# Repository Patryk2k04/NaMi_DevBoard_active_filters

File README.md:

This is an example of using goldpin connectors on the edge of the STM_proto_board https://github.com/Patryk2k04/STM_proto_board

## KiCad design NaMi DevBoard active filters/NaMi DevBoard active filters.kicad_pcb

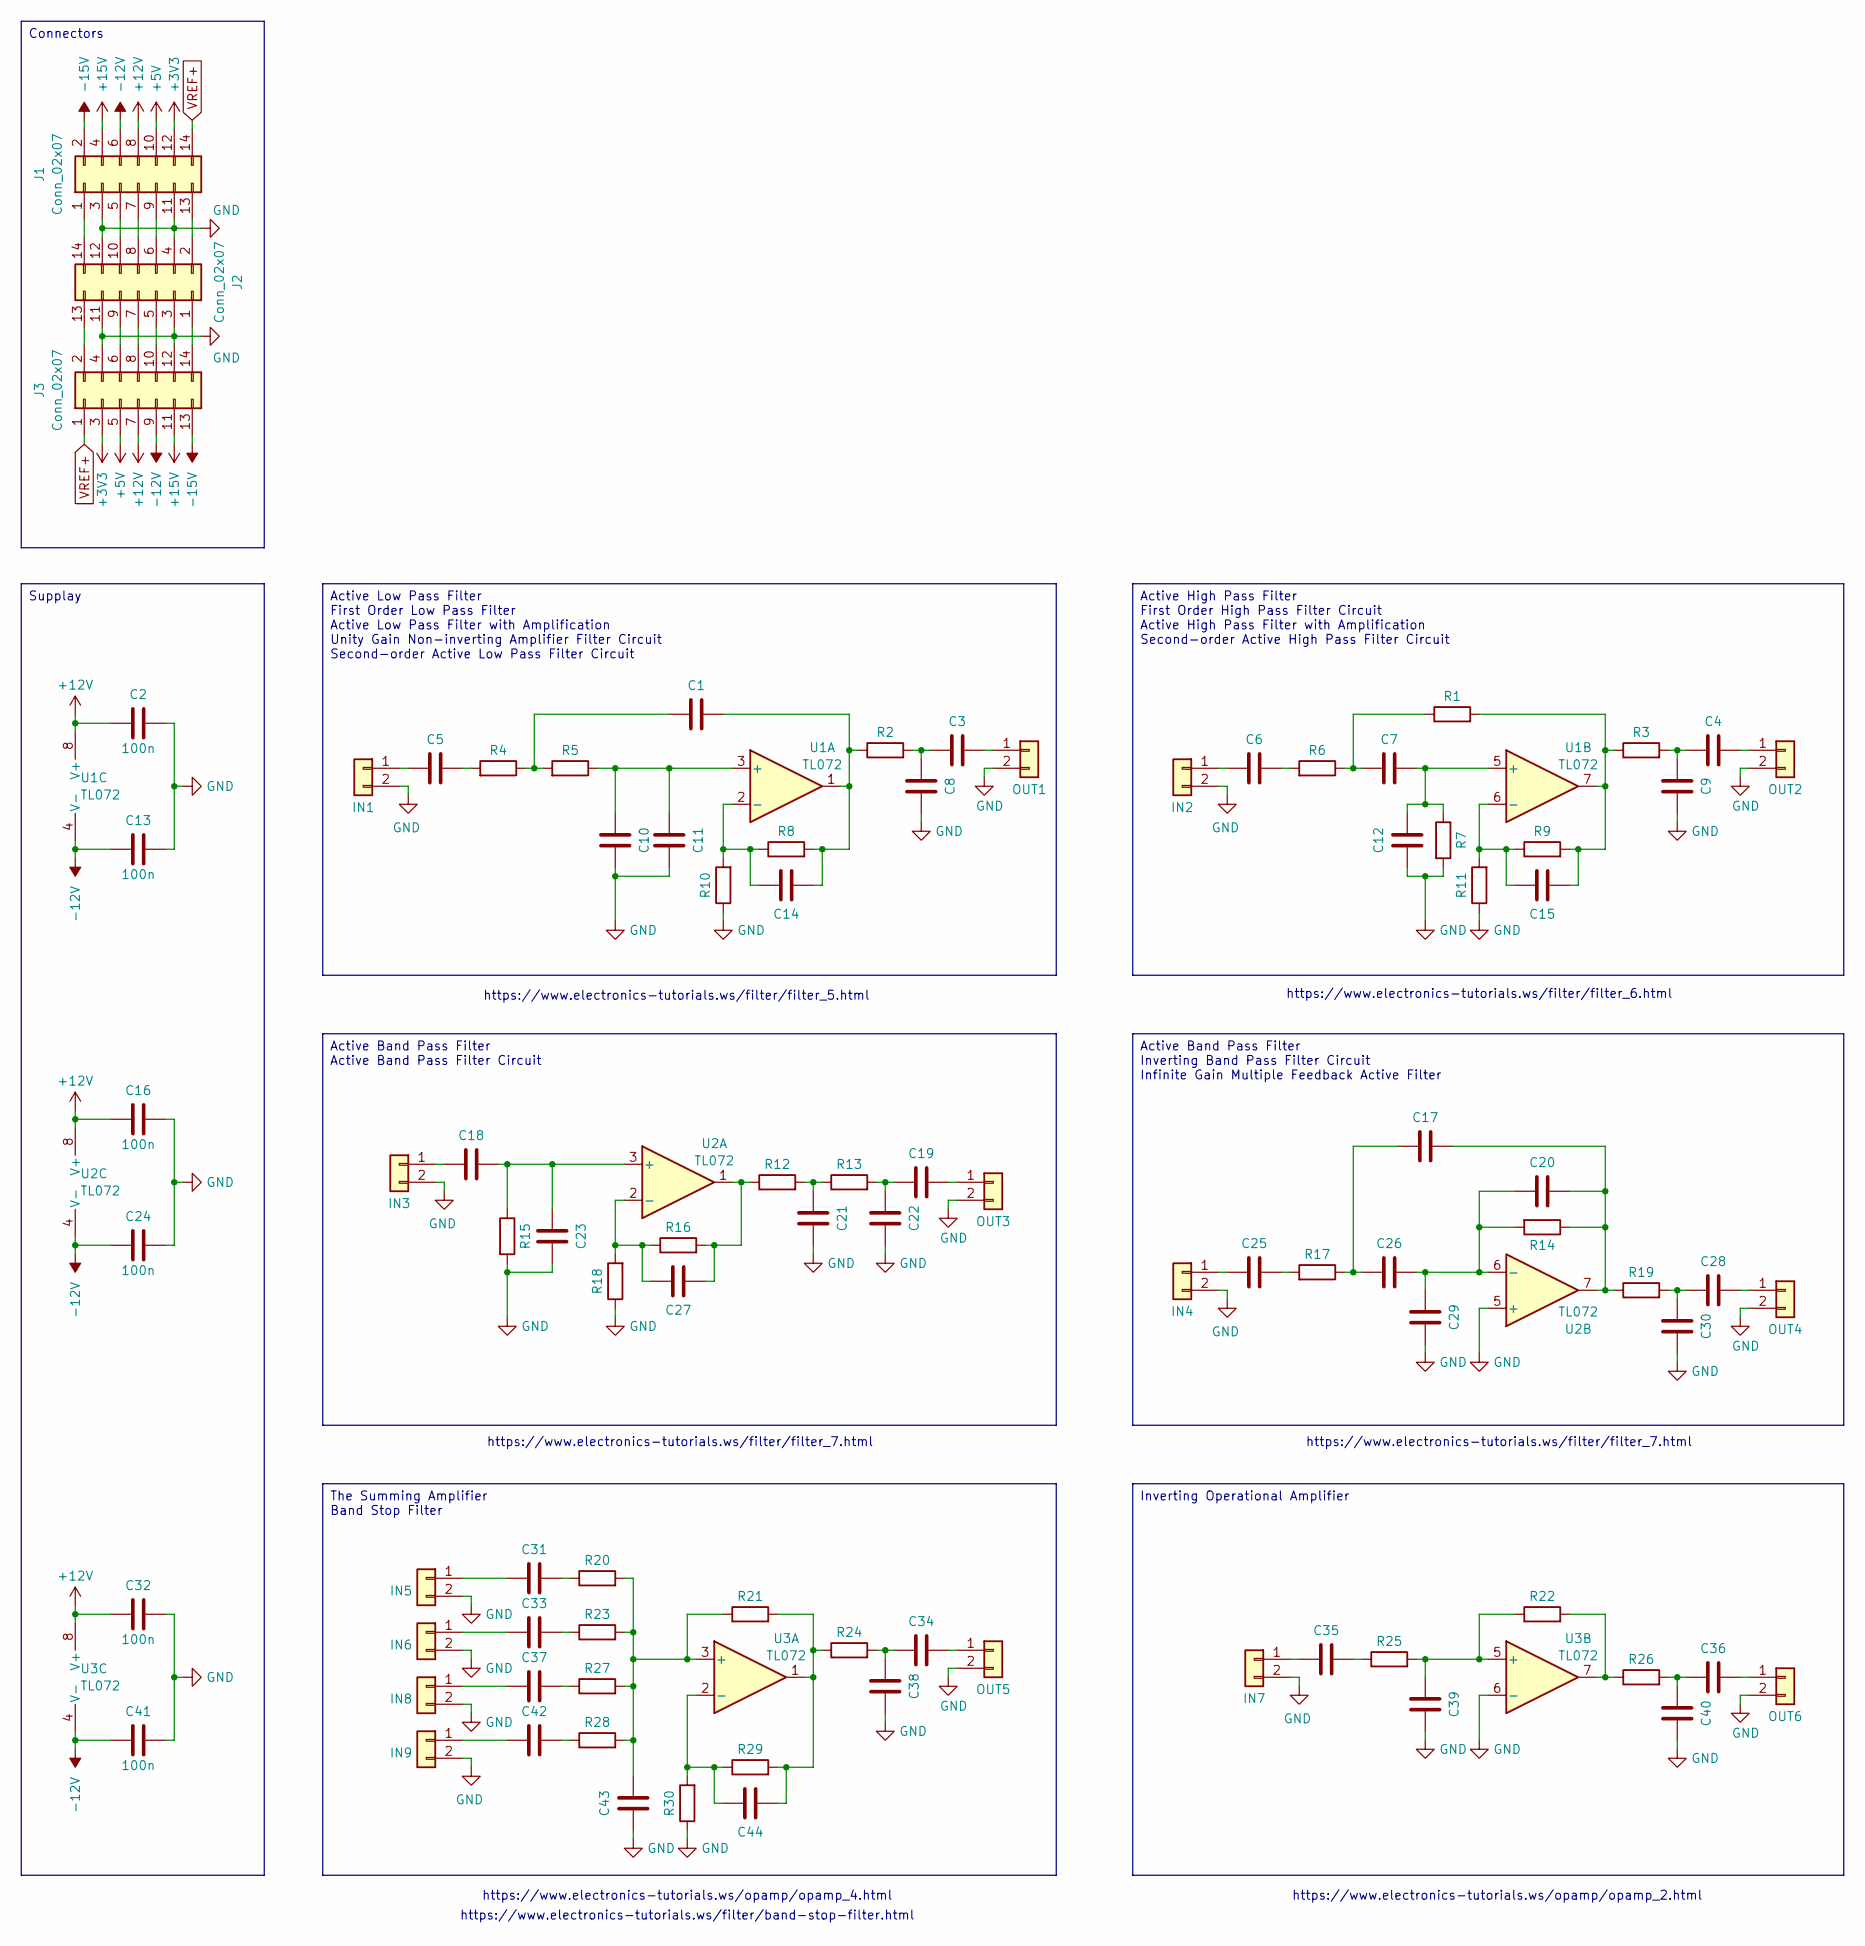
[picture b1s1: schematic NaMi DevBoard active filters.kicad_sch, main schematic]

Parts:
C1, C3, C4, C5, C6, C7, C8, C9, C10, C11, C12, C14, C15, C17, C18, C19, C20, C21, C22, C23, C25, C26, C27, C28, C29, C30, C31, C33, C34, C35, C36, C37, C38, C39, C40, C42, C43, C44: C_0603_1608Metric_Pad1.08x0.95mm_HandSolder
C2, C13, C16, C24, C32, C41: 100n; C_0603_1608Metric_Pad1.08x0.95mm_HandSolder
IN1, IN2, IN3, IN4, IN5, IN6, IN7, IN8, IN9: Conn_01x02; PinHeader_1x02_P2.54mm_Vertical
J1, J3: Conn_02x07; PinSocket_2x07_P2.54mm_Vertical
J2: Conn_02x07; PinHeader_2x07_P2.54mm_Vertical
OUT1, OUT2, OUT3, OUT4, OUT5, OUT6: Conn_01x02; PinHeader_1x02_P2.54mm_Vertical
R1, R2, R3, R4, R5, R6, R7, R8, R9, R10, R11, R12, R13, R14, R15, R16, R17, R18, R19, R20, R21, R22, R23, R24, R25, R26, R27, R28, R29, R30: R_0603_1608Metric_Pad0.98x0.95mm_HandSolder
U1, U2, U3: TL072; SOIC-8_3.9x4.9mm_P1.27mm

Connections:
+3V3: J1.12, J3.3
+5V: J1.10, J3.5
+12V: C2.1, C16.1, C32.1, J1.8, J3.7, U1.8 (V+), U2.8 (V+), U3.8 (V+)
+15V: J1.4, J3.11
-12V: C13.1, C24.1, C41.1, J1.6, J3.9, U1.4 (V-), U2.4 (V-), U3.4 (V-)
-15V: J1.2, J3.13
GND: C2.2, C8.2, C9.2, C10.2, C11.2, C12.1, C13.2, C16.2, C21.1, C22.2, C23.1, C24.2, C29.1, C30.2, C32.2, C38.2, C39.1, C40.2, C41.2, C43.1, IN1.2, IN2.2, IN3.2, IN4.2, IN5.2, IN6.2, IN7.2, IN8.2, IN9.2, J1.3, J1.11, J2.3, J2.4, J2.11, J2.12, J3.4, J3.12, OUT1.2, OUT2.2, OUT3.2, OUT4.2, OUT5.2, OUT6.2, R7.2, R10.1, R11.1, R15.2, R18.1, R30.1, U2.5 (+), U3.6 (-)
unnamed: C1.1, R4.1, R5.2
unnamed: C1.2, C14.2, R2.1, R8.2, U1.1
unnamed: C3.1, C8.1, R2.2
unnamed: C4.1, C9.1, R3.2
unnamed: C5.2, R4.2
unnamed: C6.2, R6.2
unnamed: C7.1, R1.1, R6.1
unnamed: C15.2, R1.2, R3.1, R9.2, U1.7
unnamed: C17.1, C20.1, R14.1, R19.1, U2.7
unnamed: C17.2, C26.1, R17.1
unnamed: C19.1, C22.1, R13.2
unnamed: C21.2, R12.2, R13.1
unnamed: C25.2, R17.2
unnamed: C27.2, R12.1, R16.2, U2.1
unnamed: C28.1, C30.1, R19.2
unnamed: C31.1, R20.1
unnamed: C33.1, R23.1
unnamed: C34.1, C38.1, R24.2
unnamed: C35.1, R25.1
unnamed: C36.1, C40.1, R26.2
unnamed: C37.1, R27.1
unnamed: C42.1, R28.1
unnamed: C44.2, R21.2, R24.1, R29.2, U3.1
unnamed: C5.1, IN1.1
unnamed: C6.1, IN2.1
unnamed: C18.1, IN3.1
unnamed: C25.1, IN4.1
unnamed: C31.2, IN5.1
unnamed: C33.2, IN6.1
unnamed: C35.2, IN7.1
unnamed: C37.2, IN8.1
unnamed: C42.2, IN9.1
unnamed: J1.1, J2.14
unnamed: J1.5, J2.10
unnamed: J1.7, J2.8
unnamed: J1.9, J2.6
unnamed: J1.13, J2.2
unnamed: J2.1, J3.14
unnamed: J2.5, J3.10
unnamed: J2.7, J3.8
unnamed: J2.9, J3.6
unnamed: J2.13, J3.2
unnamed: C3.2, OUT1.1
unnamed: C4.2, OUT2.1
unnamed: C19.2, OUT3.1
unnamed: C28.2, OUT4.1
unnamed: C34.2, OUT5.1
unnamed: C36.2, OUT6.1
unnamed: R22.2, R26.1, U3.7
unnamed: C10.1, C11.1, R5.1, U1.3 (+)
unnamed: C14.1, R8.1, R10.2, U1.2 (-)
unnamed: C7.2, C12.2, R7.1, U1.5 (+)
unnamed: C15.1, R9.1, R11.2, U1.6 (-)
unnamed: C18.2, C23.2, R15.1, U2.3 (+)
unnamed: C27.1, R16.1, R18.2, U2.2 (-)
unnamed: C20.2, C26.2, C29.2, R14.2, U2.6 (-)
unnamed: C43.2, R20.2, R21.1, R23.2, R27.2, R28.2, U3.3 (+)
unnamed: C44.1, R29.1, R30.2, U3.2 (-)
unnamed: C39.2, R22.1, R25.2, U3.5 (+)
VREF+: J1.14, J3.1

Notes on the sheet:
https://www.electronics-tutorials.ws/opamp/opamp_2.html
https://www.electronics-tutorials.ws/filter/filter_7.html
https://www.electronics-tutorials.ws/filter/band-stop-filter.html
https://www.electronics-tutorials.ws/filter/filter_5.html
https://www.electronics-tutorials.ws/opamp/opamp_4.html
https://www.electronics-tutorials.ws/filter/filter_6.html
Active Band Pass Filter Inverting Band Pass Filter Circuit Infinite Gain Multiple Feedback Active Filter
Inverting Operational Amplifier
Supplay
Connectors
Active Low Pass Filter First Order Low Pass Filter Active Low Pass Filter with Amplification Unity Gain Non-inverting Amplifier Filter Circuit Second-order Active Low Pass Filter Circuit
Active Band Pass Filter Active Band Pass Filter Circuit
The Summing Amplifier Band Stop Filter
Active High Pass Filter First Order High Pass Filter Circuit Active High Pass Filter with Amplification Second-order Active High Pass Filter Circuit

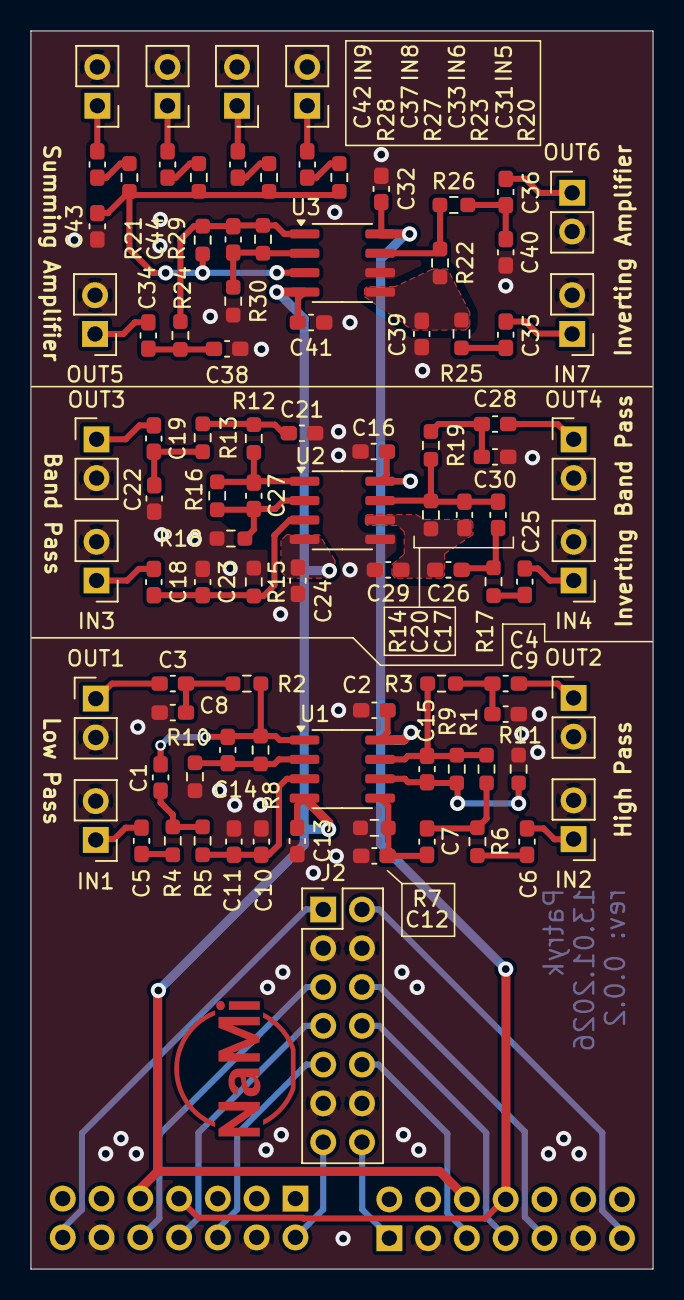
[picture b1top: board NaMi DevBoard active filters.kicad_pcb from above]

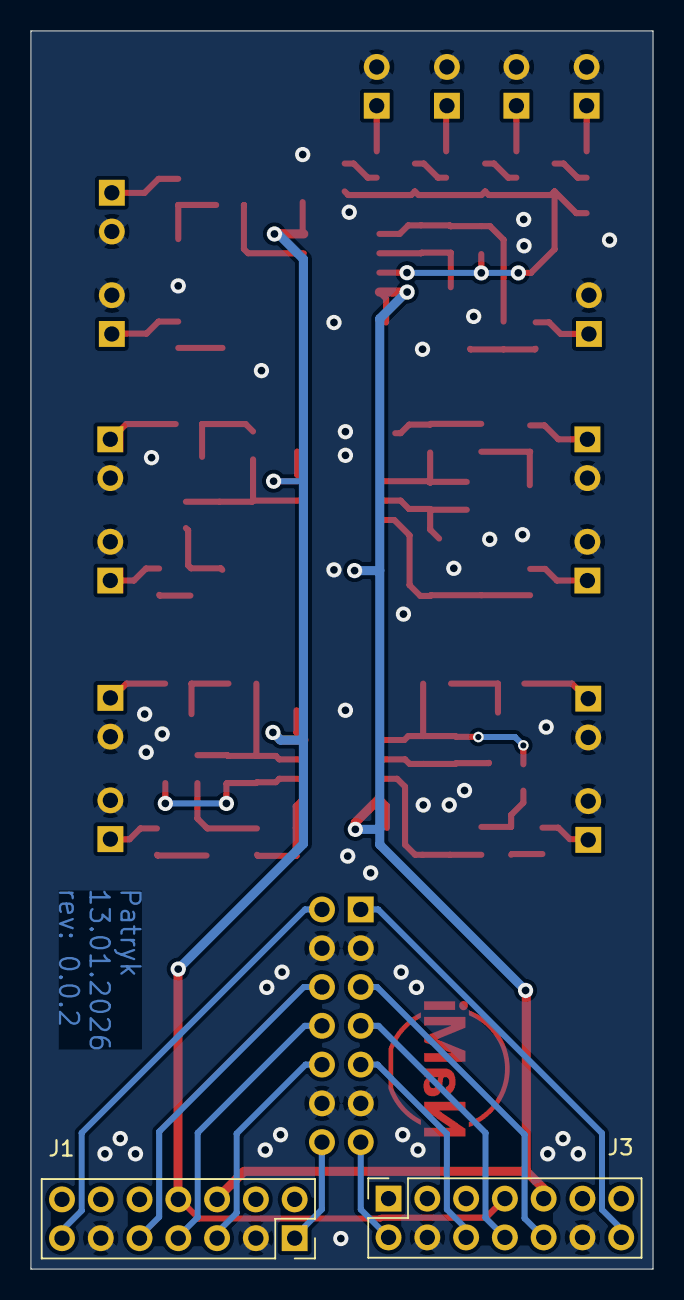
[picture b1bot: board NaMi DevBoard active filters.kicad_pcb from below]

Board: 2 copper layers, 40.7 x 81.1 mm, 95 parts (2 on the bottom side), 67 nets.

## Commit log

2025-12-22 Add all files
2025-12-22 Deleting unnecessary files
2025-12-22 Add example usage of goldpin connectors
2025-12-22 Add information on PCB and schematic
2025-12-22 Update BOM file
2026-01-13 a few corrections
2026-01-15 making PCB milling easier
2026-01-15 date change
2026-01-15 bom actualization
2026-01-19 make text bold
